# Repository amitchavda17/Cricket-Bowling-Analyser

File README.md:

# Cricket-Bowling-Analyser

Cricket Bolwing analyser is  a low cost embedded system  that can be used for analysing bolwers perfromance analysis in Cricket.The system is capable of measuring line length and speed of delivery.
The system consist of an  sensor matrix integrated with embedded system for measuring line and length of delivery and uses ultrasonic sensor for measuring the speed of dleivery.
A basic GUI is designed for  providing performance  analysis to user.

## The [Report](https://github.com/amitchavda17/Cricket-Bowling-Analyser/blob/master/Report.pdf) file contians following
* Detail explanation of project with required components and  results  
* Process of designing sensor matrix using velostat with measurments 
* Block diagram for system 
* Schematic Diagram for [PCB](https://github.com/amitchavda17/Cricket-Bowling-Analyser/tree/master/Circuit)
* Circuit diagram for sesnor arduino interfacing

## Code files
* [sensor interfacing](https://github.com/amitchavda17/Cricket-Bowling-Analyser/blob/master/sensor_matrix.ino) this file contains code for data acqusition from sensor matrix and generating results
* [Speed measrument](https://github.com/amitchavda17/Cricket-Bowling-Analyser/blob/master/speed_measurment.ino) code for speed measrument using ultrasonic sensor
* [Live visualization](https://github.com/amitchavda17/Cricket-Bowling-Analyser/blob/master/live_visualization.pde) Processing3 code written in java for visualzing results in real time
* [GUI](https://github.com/amitchavda17/Cricket-Bowling-Analyser/tree/master/GUI) using pyQt in python and webased using html

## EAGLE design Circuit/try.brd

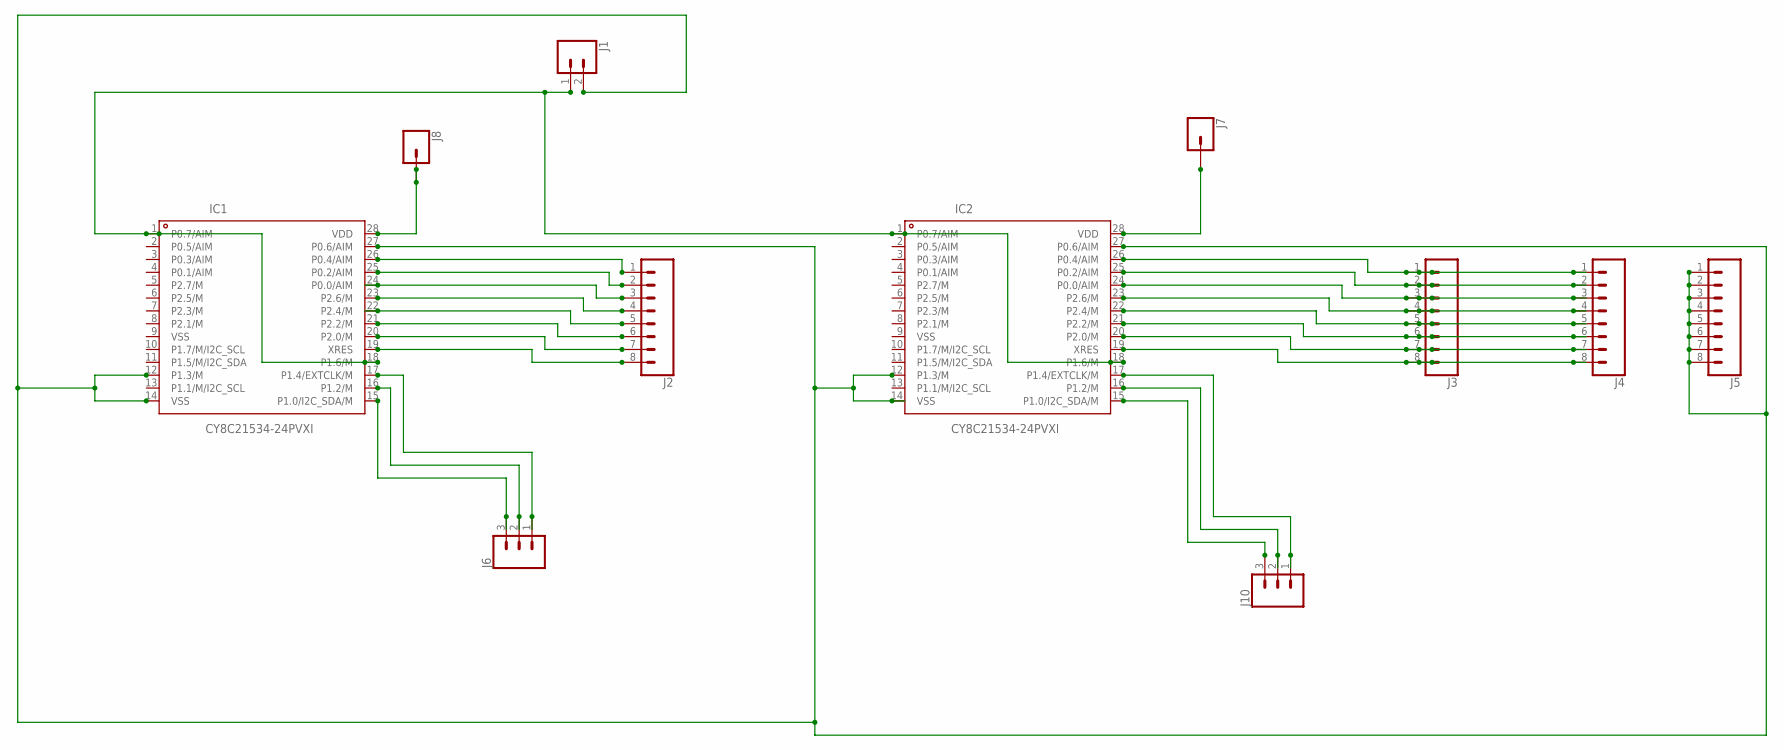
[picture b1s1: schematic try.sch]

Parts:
IC1, IC2: CY8C21534-24PVXI; SSOP28
J1: CONN_02PTH3; 1X02_LONGPADS
J2, J3, J4, J5: CONN_08LONGPADS; 1X08_LONGPADS
J6, J10: CONN_03LONGPADS; 1X03_LONGPADS
J7, J8: CONN_01PTH_LONGPAD; 1X01_LONGPAD

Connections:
unnamed: IC1.17 (P1.4/EXTCLK/M), J6.1
unnamed: IC2.15 (P1.0/I2C_SDA/M), J10.3
unnamed: IC1.12 (P1.3/M), IC1.14 (VSS), IC1.27 (P0.6/AIM), IC2.12 (P1.3/M), IC2.14 (VSS), IC2.27 (P0.6/AIM), J1.2, J5.1, J5.2, J5.3, J5.4, J5.5, J5.6, J5.7, J5.8
unnamed: IC1.26 (P0.4/AIM), J2.1
unnamed: IC1.25 (P0.2/AIM), J2.2
unnamed: IC1.24 (P0.0/AIM), J2.3
unnamed: IC1.23 (P2.6/M), J2.4
unnamed: IC1.22 (P2.4/M), J2.5
unnamed: IC1.21 (P2.2/M), J2.6
unnamed: IC1.20 (P2.0/M), J2.7
unnamed: IC1.19 (XRES), J2.8
unnamed: IC2.26 (P0.4/AIM), J3.1, J4.1
unnamed: IC2.25 (P0.2/AIM), J3.2, J4.2
unnamed: IC2.24 (P0.0/AIM), J3.3, J4.3
unnamed: IC2.23 (P2.6/M), J3.4, J4.4
unnamed: IC2.22 (P2.4/M), J3.5, J4.5
unnamed: IC2.21 (P2.2/M), J3.6, J4.6
unnamed: IC2.20 (P2.0/M), J3.7, J4.7
unnamed: IC2.19 (XRES), J3.8, J4.8
unnamed: IC1.1 (P0.7/AIM), IC1.18 (P1.6/M), IC2.1 (P0.7/AIM), IC2.18 (P1.6/M), J1.1
unnamed: IC1.28 (VDD), J8.1
unnamed: IC2.28 (VDD), J7.1
unnamed: IC1.15 (P1.0/I2C_SDA/M), J6.3
unnamed: IC1.16 (P1.2/M), J6.2
unnamed: IC2.16 (P1.2/M), J10.2
unnamed: IC2.17 (P1.4/EXTCLK/M), J10.1

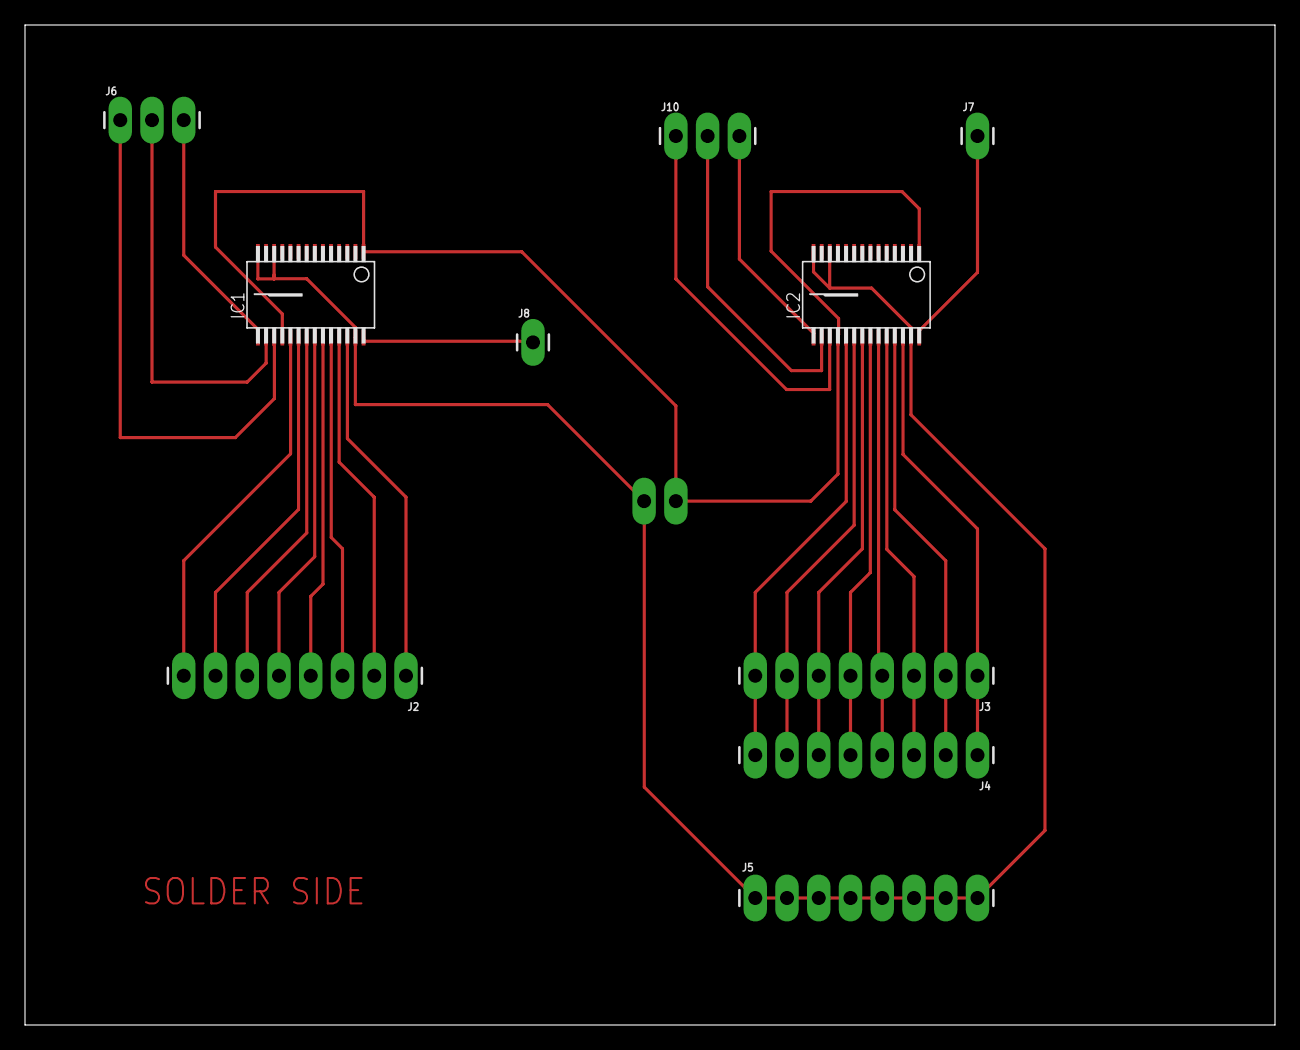
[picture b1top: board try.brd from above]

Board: 2 copper layers, 100.0 x 80.0 mm, 11 parts (1 on the bottom side), 26 nets.

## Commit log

2019-11-18 Updated read.md
2019-11-18 Final report for Cricket Bowling analyser
2019-11-18 arduino file of data acquisiton from sensor matrix
2019-11-18 Arduino code for speed measurment
2019-11-18 processing3 code for live visualization
2019-11-18 Code for user interface
2019-11-18 Circuit pcb schematic

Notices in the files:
parts and their libraries:
SparkFun-Connectors: Licensing: Creative Commons ShareAlike 4.0 International - https://creativecommons.org/licenses/by-sa/4.0
